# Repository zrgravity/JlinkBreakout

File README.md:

# JlinkBreakout

Segger Jlink to Tag-Connect/SWD breakout board.

## [V2](V2/)
Notes:
 - Use a right-angle 2 row, 20 position 0.1" (2.54mm) female header/socket
     + https://lcsc.com/product-detail/Pin-Header-Female-Header_Ckmtw-Shenzhen-Cankemeng-C124406_C124406.html

## [V3](V3/)
- Adds a voltage regulator with selectable output voltage (3.3V, 2.5V, 1.8V, External power)
- JST-XH connector for SWD
- 2x3 IDC Tag-connect header
- JTAG connector is standard 2 row, 20 position 0.1" (2.54mm) female header/socker, mounted on pcb edge
    + https://lcsc.com/product-detail/Pin-Header-Female-Header_BOOMELE-Boom-Precision-Elec-C30867_C30867.html
        * Pin thickness: 0.32mm to .064mm
        * Pin-pin clearance: 2.22mm to 1.9mm
    + Standard 1.6mm (0.062") PCB should be solderable, but there will be a small gap, or 2mm (0.079") PCB would leave less clearance

## [V3 - wire pads](/V3-wire-pads/)
- Solder jumpers to select voltage regulator output voltage
- Wire solderable edge connection for SWD
    + Also compatible with standard 0.1" headers
- Connector for power input to DUT (or access to output from regulator)

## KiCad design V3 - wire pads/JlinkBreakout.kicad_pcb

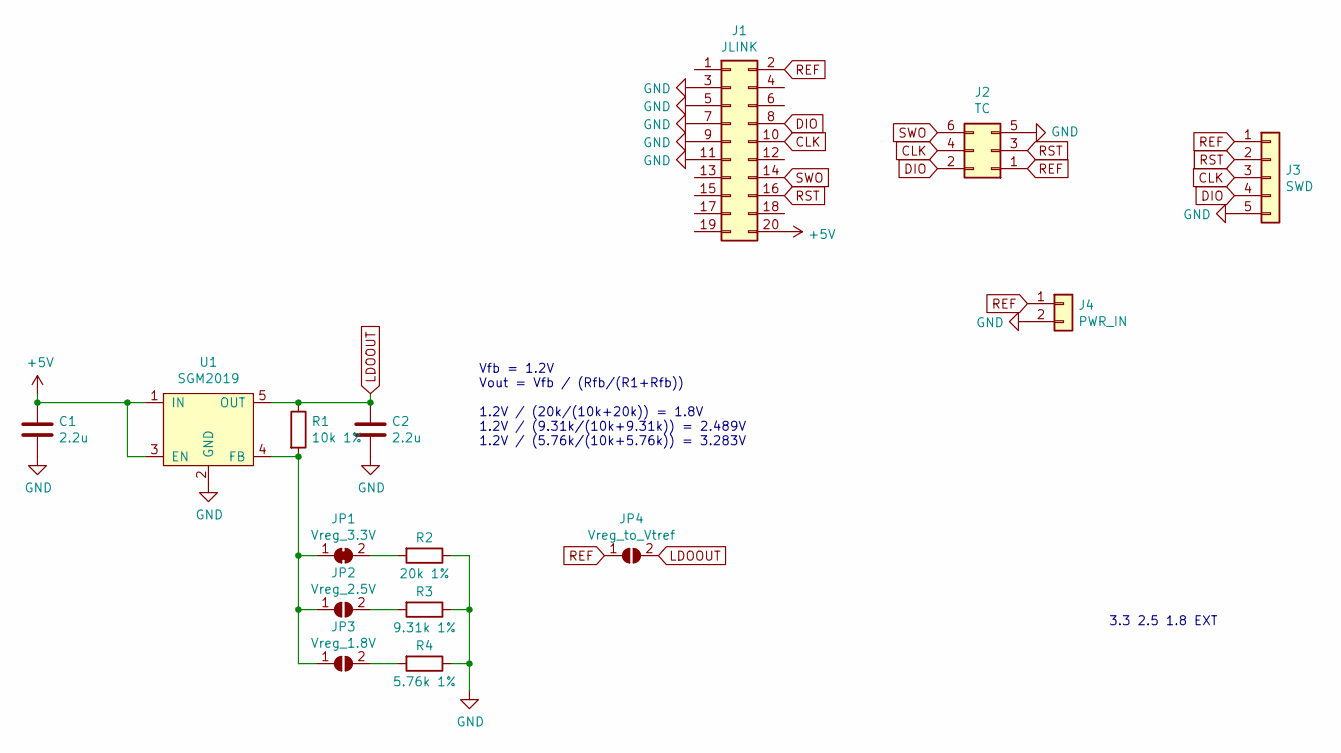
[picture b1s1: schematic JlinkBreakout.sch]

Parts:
C1: 2.2u; C_0805_2012Metric; LCSC C49217
C2: 2.2u; C_0805_2012Metric
J1: JLINK; conn_02x10_edge; LCSC C30867
J2: TC; IDC-Header_2x03_P2.54mm_Vertical; LCSC C11214
J3: SWD; conn_edge_PTH_2.54mm_2x5_05; LCSC C161872
J4: PWR_IN; conn_edge_PTH_2.54mm_2x5_02
JP1: Vreg_3.3V; SolderJumper-2_P1.3mm_Bridged_RoundedPad1.0x1.5mm
JP2: Vreg_2.5V; SolderJumper-2_P1.3mm_Open_RoundedPad1.0x1.5mm
JP3: Vreg_1.8V; SolderJumper-2_P1.3mm_Open_RoundedPad1.0x1.5mm
JP4: Vreg_to_Vtref; SolderJumper-2_P1.3mm_Open_RoundedPad1.0x1.5mm
R1: 10k 1%; R_0603_1608Metric; LCSC C25804
R2: 20k 1%; R_0603_1608Metric
R3: 9.31k 1%; R_0603_1608Metric
R4: 5.76k 1%; R_0603_1608Metric
U1: SGM2019; SOT-23-5; LCSC C24330

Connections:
+5V: C1.1, J1.20, U1.1 (IN), U1.3 (EN)
CLK: J1.10, J2.4, J3.3
DIO: J1.8, J2.2, J3.4
GND: C1.2, C2.2, J1.3, J1.5, J1.7, J1.9, J1.11, J2.5, J3.5, J4.2, R2.1, R3.1, R4.1, U1.2 (GND)
LDOOUT: C2.1, JP4.2 (B), R1.1, U1.5 (OUT)
unnamed: JP1.1 (A), JP2.1 (A), JP3.1 (A), R1.2, U1.4 (FB)
unnamed: JP1.2 (B), R2.2
unnamed: JP2.2 (B), R3.2
unnamed: JP3.2 (B), R4.2
REF: J1.2, J2.1, J3.1, J4.1, JP4.1 (A)
RST: J1.16, J2.3, J3.2
SWO: J1.14, J2.6

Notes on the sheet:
3.3 2.5 1.8 EXT
Vfb = 1.2V Vout = Vfb / (Rfb/(R1+Rfb)) 1.2V / (20k/(10k+20k)) = 1.8V 1.2V / (9.31k/(10k+9.31k)) = 2.489V 1.2V / (5.76k/(10k+5.76k)) = 3.283V

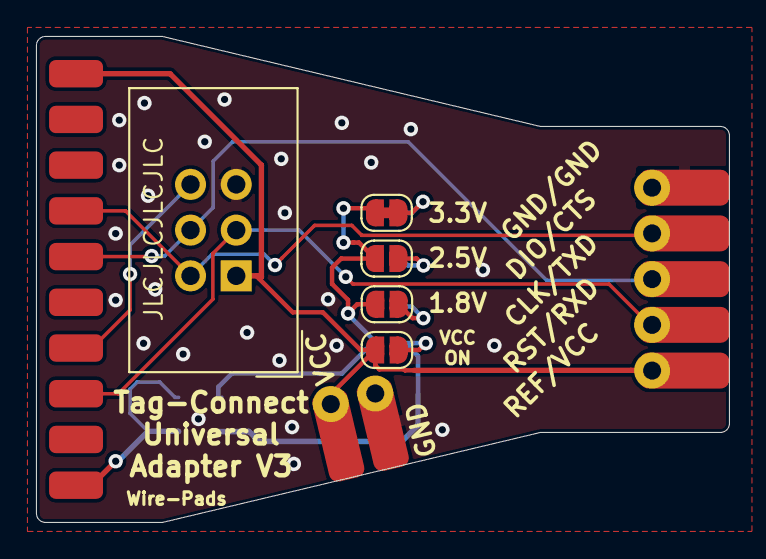
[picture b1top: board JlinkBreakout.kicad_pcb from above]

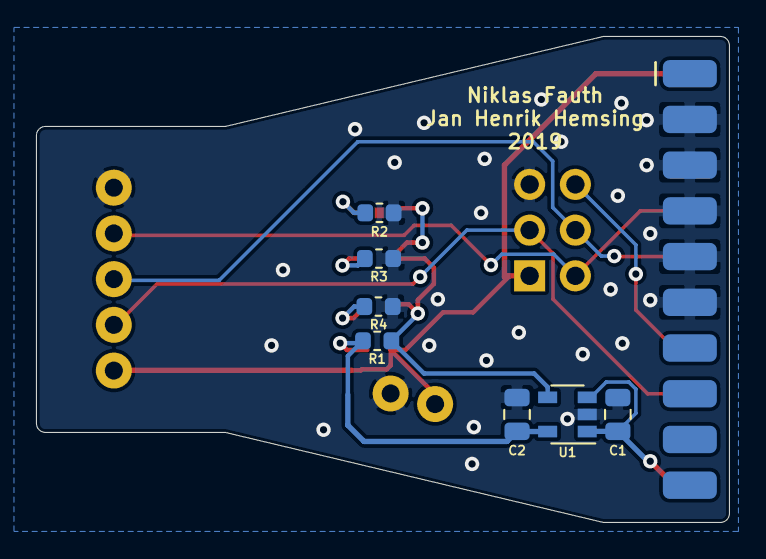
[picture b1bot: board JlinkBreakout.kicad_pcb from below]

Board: 2 copper layers, 38.5 x 27.0 mm, 15 parts (7 on the bottom side), 12 nets.

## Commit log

2020-07-23 V3-wire pads: create, replace switch with solder jumpers, connector
2020-07-23 Route v3-wire pads PCB, add to README
    Uses solder jumpers to select voltage, external power input/output pads
2020-07-23 Rename folder and image to fix README
2020-07-23 Crop image
2020-07-23 Backup footprints
2020-07-23 Add LCSC part numbers to resistors
2020-07-23 Ignore gerber files
    Should go in releases instead
